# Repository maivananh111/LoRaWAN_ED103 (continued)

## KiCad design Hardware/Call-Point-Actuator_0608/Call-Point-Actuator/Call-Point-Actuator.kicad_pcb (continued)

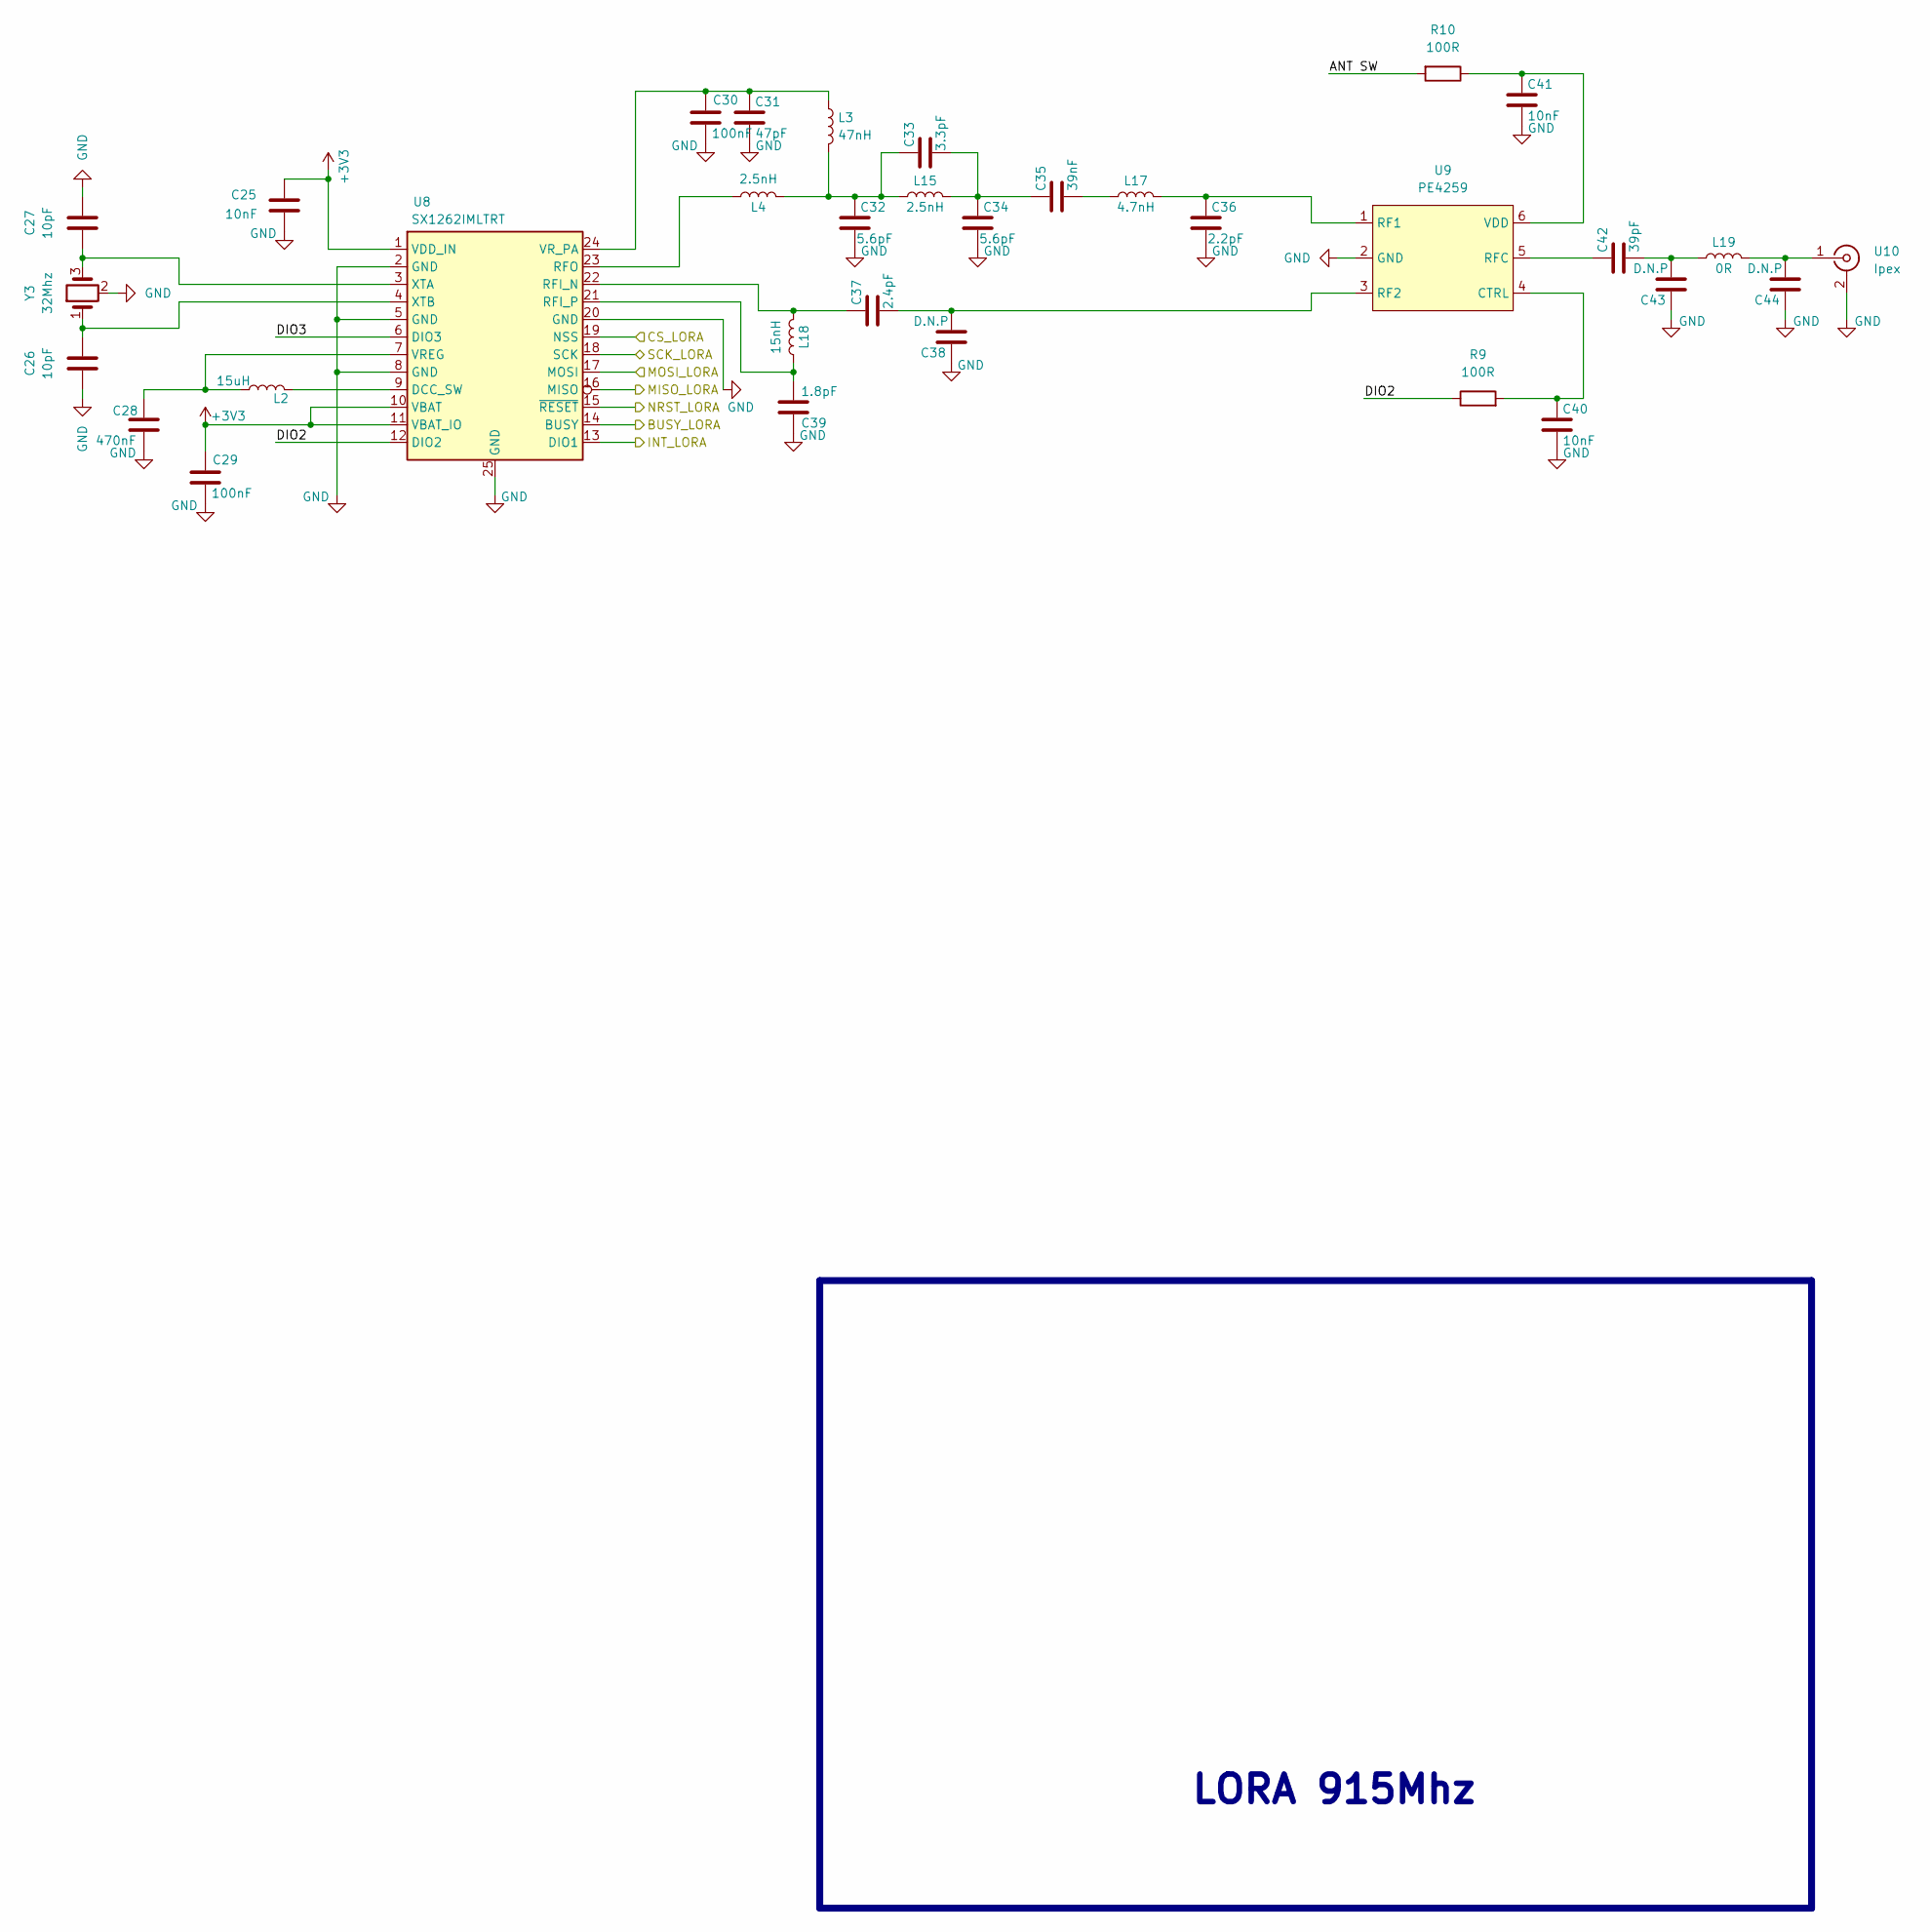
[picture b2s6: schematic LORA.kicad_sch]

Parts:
C25, C40, C41: 10nF; C_0603_1608Metric; JLC C43253
C26, C27: 10pF; C_0603_1608Metric; JLC C1634
C28: 470nF; C_0603_1608Metric; JLC C77572
C29, C30: 100nF; C_0603_1608Metric; JLC C14663
C31: 47pF; C_0603_1608Metric; JLC C105622
C32, C34: 5.6pF; C_0603_1608Metric; JLC C1674
C33: 3.3pF; C_0603_1608Metric; JLC C1660
C35: 39nF; C_0603_1608Metric; JLC C107091
C36: 2.2pF; C_0603_1608Metric; JLC C1651
C37: 2.4pF; C_0603_1608Metric; JLC C27741
C38, C43, C44: D.N.P; C_0603_1608Metric
C39: 1.8pF; C_0603_1608Metric; JLC C1640
C42: 39pF; C_0603_1608Metric; JLC C107049
L2: 15uH; L_0603; JLC C57838
L3: 47nH; L_0603; JLC C29683
L4, L15: 2.5nH; L_0603; JLC C370234
L17: 4.7nH; L_0603; JLC C1030
L18: 15nH; L_0603; JLC C23651
L19: 0R; L_0603; JLC C21189
R9, R10: 100R; L_0603_1608Metric; JLC C22775
U8: SX1262IMLTRT; QFN-24-1EP_4x4mm_P0.5mm_EP2.6x2.6mm
U9: PE4259; SOT-363_SC-70-6; JLC C470892
U10: Ipex; Conn_IPEX_ANT; JLC C496552
Y3: 32Mhz; Crystal_SMD_3225-4Pin_3.2x2.5mm; JLC C9009

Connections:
+3V3: C25.1, C29.1, U8.1 (VDD_IN), U8.10 (VBAT), U8.11 (VBAT_IO); also elsewhere on the board
/LORA/ANT SW: R10.2
/LORA/BUSY_LORA: U8.14 (BUSY); also elsewhere on the board
/LORA/CS_LORA: U8.19 (NSS); also elsewhere on the board
/LORA/DIO2: R9.1, U8.12 (DIO2)
/LORA/DIO3: U8.6 (DIO3)
/LORA/INT_LORA: U8.13 (DIO1); also elsewhere on the board
/LORA/MISO_LORA: U8.16 (MISO); also elsewhere on the board
/LORA/MOSI_LORA: U8.17 (MOSI); also elsewhere on the board
/LORA/NRST_LORA: U8.15 (~RESET); also elsewhere on the board
/LORA/SCK_LORA: U8.18 (SCK); also elsewhere on the board
GND: C25.2, C26.1, C27.2, C28.2, C29.2, C30.2, C31.2, C32.2, C34.2, C36.2, C38.1, C39.1, C40.2, C41.2, C43.1, C44.1, U8.2 (GND), U8.5 (GND), U8.8 (GND), U8.20 (GND), U8.25 (GND), U9.2 (GND), U10.2, U10.3, Y3.2, Y3.4; also elsewhere on the board
unnamed: C32.1, C33.1, L3.2, L4.2, L15.1
unnamed: C33.2, C34.1, C35.1, L15.2
unnamed: C35.2, L17.1
unnamed: C42.2, C43.2, L19.1
unnamed: C44.2, L19.2, U10.1
unnamed: L2.2, U8.9 (DCC_SW)
unnamed: C37.1, L18.2, U8.22 (RFI_N)
unnamed: C39.2, L18.1, U8.21 (RFI_P)
unnamed: L4.1, U8.23 (RFO)
unnamed: C28.1, L2.1, U8.7 (VREG)
unnamed: C30.1, C31.1, L3.1, U8.24 (VR_PA)
unnamed: C27.1, U8.3 (XTA), Y3.3
unnamed: C26.2, U8.4 (XTB), Y3.1
unnamed: C40.1, R9.2, U9.4 (CTRL)
unnamed: C36.1, L17.2, U9.1 (RF1)
unnamed: C37.2, C38.2, U9.3 (RF2)
unnamed: C42.1, U9.5 (RFC)
unnamed: C41.1, R10.1, U9.6 (VDD)

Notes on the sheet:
LORA 915Mhz

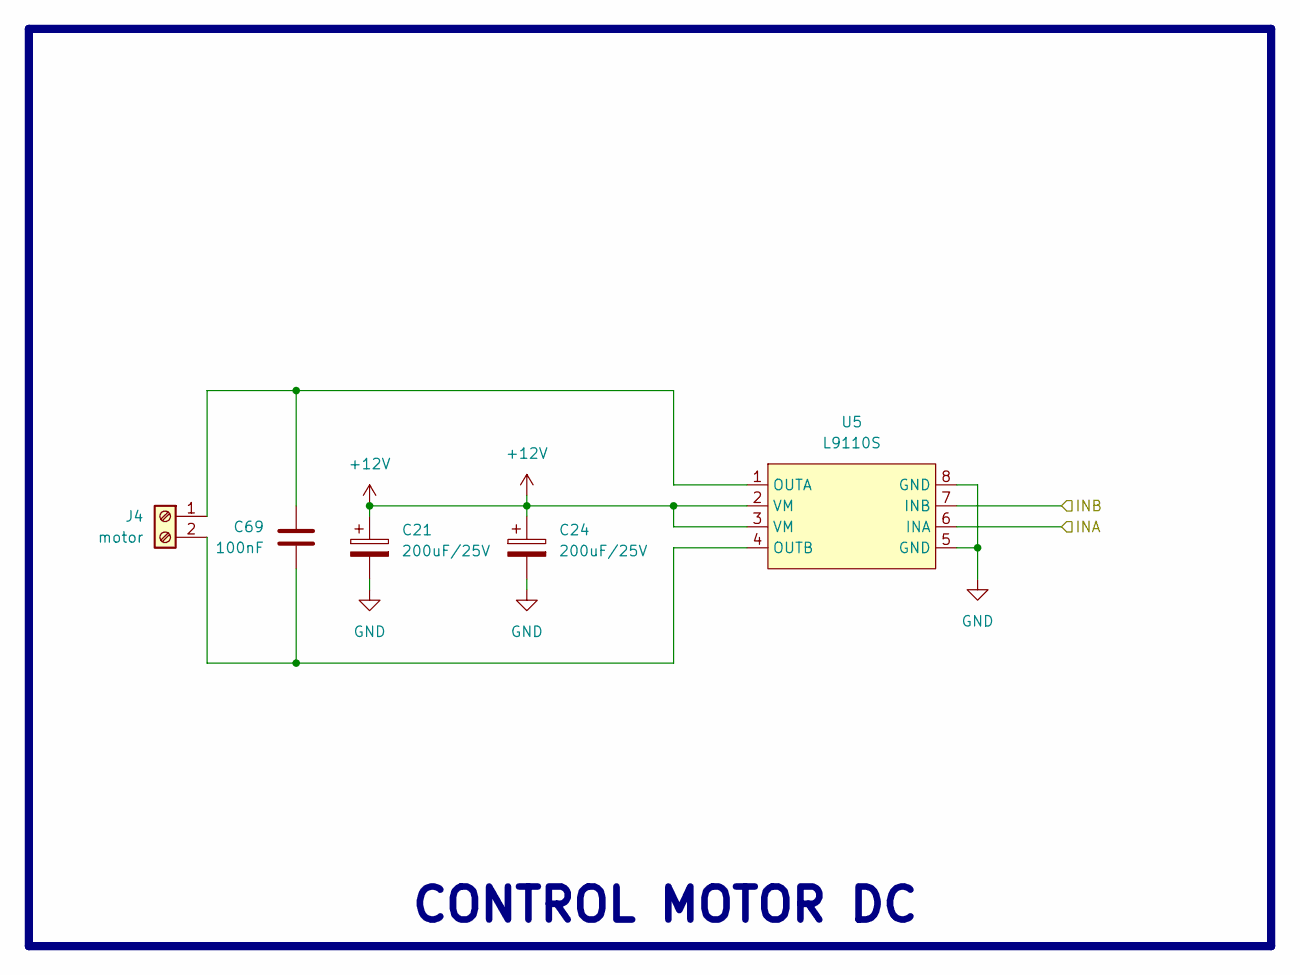
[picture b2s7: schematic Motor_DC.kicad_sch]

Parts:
C21, C24: 200uF/25V; C_TANTA_7343_CASE_E; JLC C132558
C69: 100nF; C_1206_3216Metric; JLC C525187
J4: motor; JST_PH_S2B-PH-SM4-TB_1x02-1MP_P2.00mm_Horizontal
U5: L9110S; SOP-8_3.9x4.9mm_P1.27mm; JLC C19272815

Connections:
+12V: C21.1, C24.1, U5.2 (VM), U5.3 (VM); also elsewhere on the board
/MCU/INA: U5.6 (INA); also elsewhere on the board
/MCU/INB: U5.7 (INB); also elsewhere on the board
GND: C21.2, C24.2, U5.5 (GND), U5.8 (GND); also elsewhere on the board
unnamed: C69.1, J4.1, U5.1 (OUTA)
unnamed: C69.2, J4.2, U5.4 (OUTB)

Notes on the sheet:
CONTROL MOTOR DC

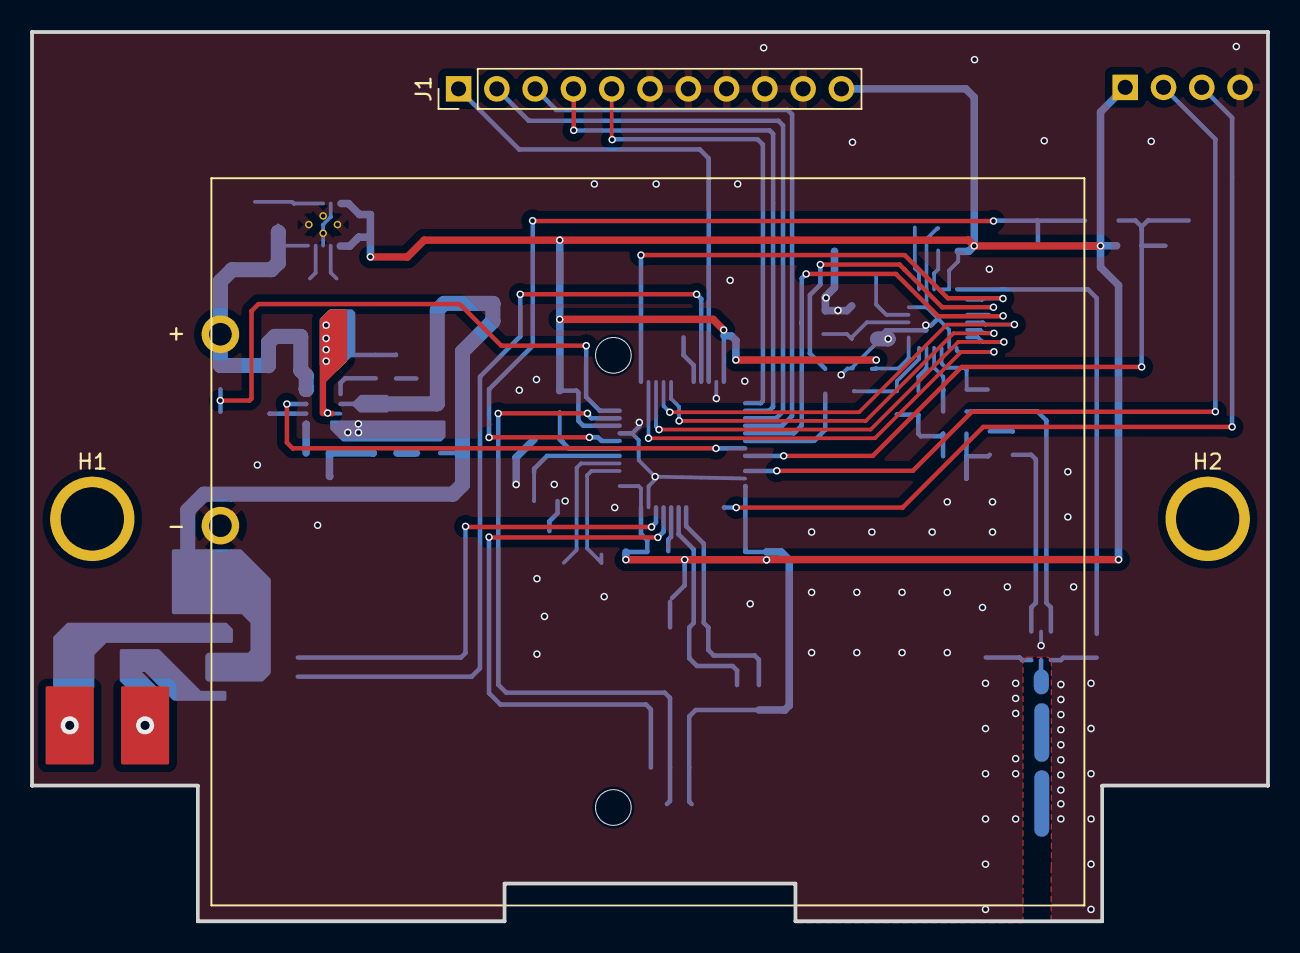
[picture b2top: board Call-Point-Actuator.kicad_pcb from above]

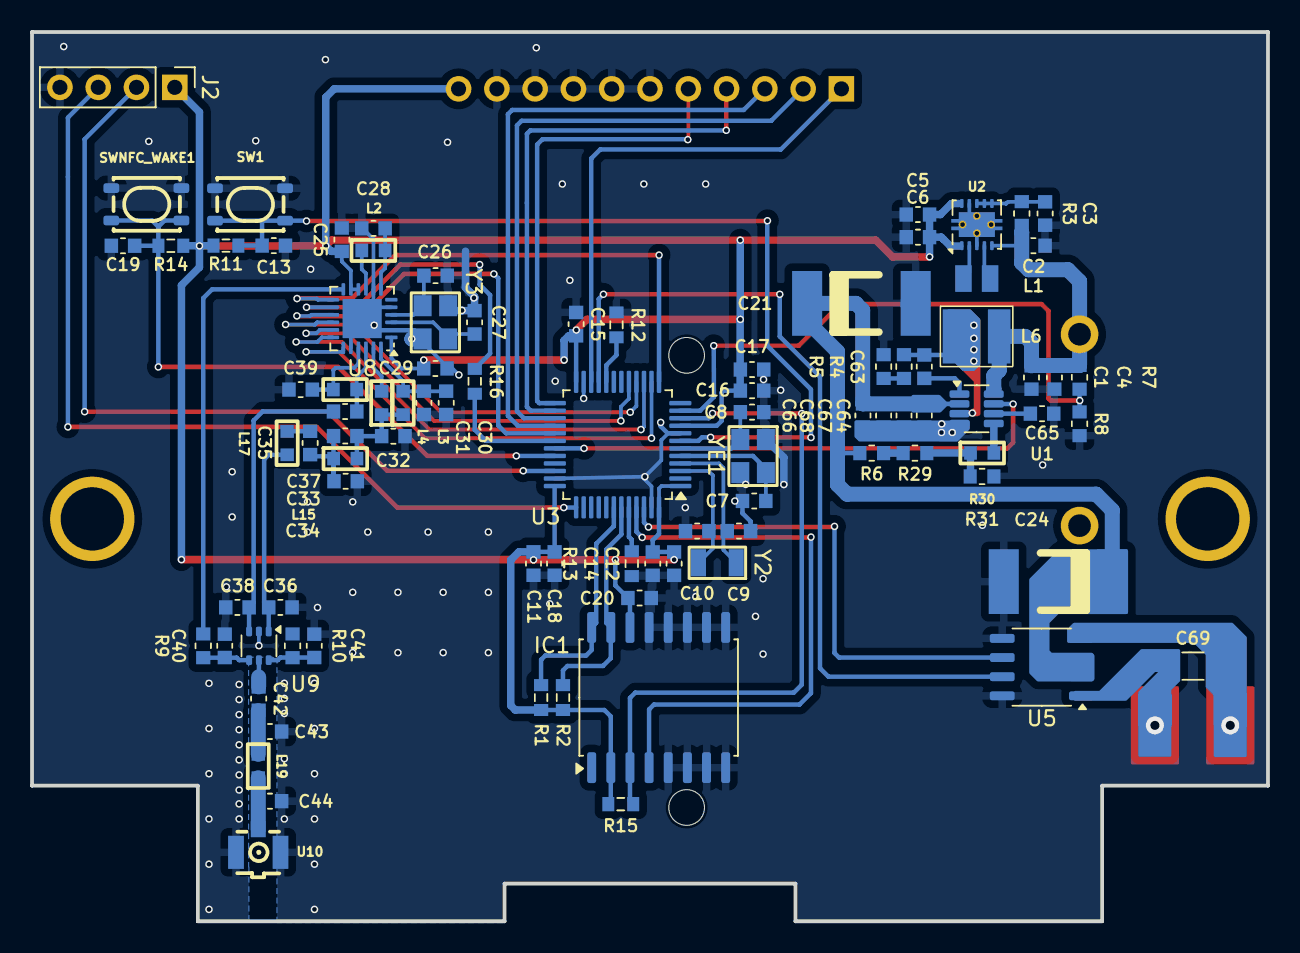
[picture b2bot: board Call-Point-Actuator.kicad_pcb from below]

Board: 2 copper layers, 82.0 x 59.0 mm, 95 parts (91 on the bottom side), 66 nets.

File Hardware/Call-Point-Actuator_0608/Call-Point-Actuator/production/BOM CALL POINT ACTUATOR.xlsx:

NAME | VALUE | FOOTPRINT | JLC | DigiKey Part Number
BT1 | Battery | DienLIB:BAT_BC3AAPC |  | BC3AAPC-ND
> C1, C4, C66-C68 | 22uF | C_0603_1608Metric | C84419
> C2, C5, C6 | 10uF | C_0603_1608Metric | C91150
> C3, C12-C16, C19, C20, C29, C30, C63, C64 | 100nF | C_0603_1608Metric | C116838
> C7, C8 | 12pF | C_0603_1608Metric | C1642
> C9, C10 | 9pF | C_0603_1608Metric | C513579
> C11, C65 | 4.7uF | C_0603_1608Metric | C76615
> C17, C25, C40, C41 | 10nF | C_0603_1608Metric | C43253
C18 | 1uF | C_0603_1608Metric | C126631
> C21, C24 | 200uF/25V | SANG_LIB_FP:C_TANTA_7343_CASE_E | C132558
> C26, C27 | 10pF | C_0603_1608Metric | C1634
C28 | 470nF | C_0603_1608Metric | C77572
C31 | 47pF | C_0603_1608Metric | C105622
> C32, C34 | 5.6pF | C_0603_1608Metric | C1674
C33 | 3.3pF | C_0603_1608Metric | C1660
C35 | 39nF | C_0603_1608Metric | C107091
C36 | 2.2pF | C_0603_1608Metric | C1651
C37 | 2.4pF | C_0603_1608Metric | C27741
C39 | 1.8pF | C_0603_1608Metric | C1640
C42 | 39pF | C_0603_1608Metric | C107049
C69 | 100nF | C_1206_3216Metric | C525187
IC1 | RTC_DS3231M | SOIC-16W_7.5x10.3mm_P1.27mm | NPN
J1 | Conn_01x11_Pin | PinHeader_1x11_P2.54mm_Vertical | C5116357
L1 | 2.2uH/1.5A | L_0806 | C439304
L2 | 15uH | L_0603 | C57838
L3 | 47nH | L_0603 | C29683
> L4, L15 | 2.5nH | L_0603 | C370234
L6 | 4.7uH | L_4040 | C167874
L17 | 4.7nH | L_0603 | C1030
L18 | 15nH | L_0603 | C23651
L19 | 0R | L_0603 | C21189
> R1, R2 | 4k7 | R_0603_1608Metric | C23162
> R3, R9, R10 | 100R | R_0603_1608Metric | C5123580
R6 | 680k | R_0603_1608Metric | C25822
R7 | 100k | R_0603_1608Metric | C667147
R8 | 200k | R_0603_1608Metric | C335089
> R11-R15 | 10k | R_0603_1608Metric | C25804
> R16, R30 | 0R | R_0603_1608Metric | C304185
R29 | 2k | R_0603_1608Metric | C72817
R31 | 62k | R_0603_1608Metric | C432812
> SW1, SWNFC_WAKE1 | SW_Tactile | SW_SPST_PTS810 | C221896
U1 | MP3437 | TSOT-23-8 |  | 1589-MP3437GJ-ZTR-ND - Tape & Reel (TR)
U2 | TPS63001 (fixed 3v3) | Package_SON:Texas_DRC0010J_ThermalVias | C28060
U3 | STM32U031C8T6 | Package_QFP:LQFP-48_7x7mm_P0.5mm |  | 497-STM32U031C8T6-ND
U5 | L9110S | Package_SO:SOP-8_3.9x4.9mm_P1.27mm | C19272815
U8 | SX1262IMLTRT | Package_DFN_QFN:QFN-24-1EP_4x4mm_P0.5mm_EP2.6x2.6mm |  | SX1262IMLTRTTR-ND - Tape & Reel (TR)
U9 | PE4259 | Package_TO_SOT_SMD:SOT-363_SC-70-6 | C470892
U10 | Ipex | DienLIB:Conn_IPEX_ANT | C496552
Y2 | 32.768kHz | Crystal_SMD_3215-2Pin_3.2x1.5mm | C620155
Y3 | 32Mhz | Crystal_SMD_3225-4Pin_3.2x2.5mm | C9009
Y1 | 8Mhz | Crystal_SMD_3225-4Pin_3.2x2.5mm | C400090

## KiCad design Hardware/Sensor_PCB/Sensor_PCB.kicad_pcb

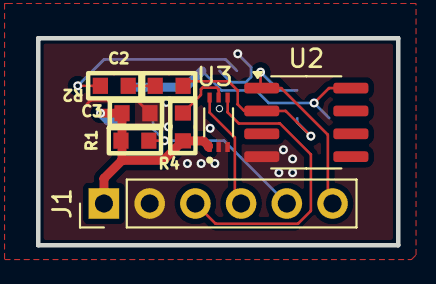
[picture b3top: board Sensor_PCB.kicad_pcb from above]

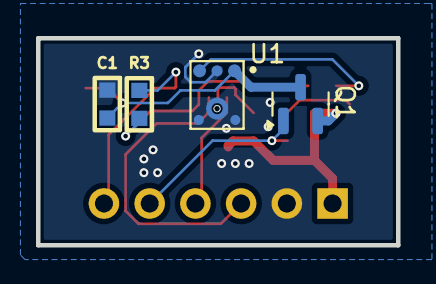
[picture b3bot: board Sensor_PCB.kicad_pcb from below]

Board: 2 copper layers, 20.0 x 11.5 mm, 12 parts (4 on the bottom side), 11 nets.

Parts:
C1, C2, C3: 100nF; C_0603
J1: 2.54; PinHeader_1x06_P2.54mm_Vertical
Q1: P_Mosfet; SOT-23
R1, R2, R3: 100k; R_0603
R4: 4k7; R_0603
U1: CMM-3729AB-38108-TR; MIC_CMM-3729AB-38108-TR
U2: LM358; SOIC-8_3.9x4.9mm_P1.27mm
U3: BH1750FVI-TR; XDCR_BH1750FVI-TR

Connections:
+3V3: C3.1, J1.1, Q1.2 (S), R1.1, R4.1, U3.1 (VCC)
/BH1750_SCL: J1.4, U3.6 (SCL)
/BH1750_SDA: J1.3, U3.4 (SDA)
/EN_Sound_sensor: J1.5, Q1.1 (G), R1.2
/Sound_sensor: J1.6, R3.2, U2.1
GND: C1.2, C3.2, J1.2, U1.2 (GND), U1.3 (GND), U1.5 (GND), U1.6 (GND), U2.4 (V-), U3.2 (ADDR), U3.3 (GND)
unnamed: C2.1, R2.1
unnamed: C1.1, Q1.3 (D), U1.1 (VDD), U2.8 (V+)
unnamed: C2.2, U1.4 (OUTPUT)
unnamed: R2.2, R3.1, U2.2 (-)
unnamed: R4.2, U3.5 (DVI)

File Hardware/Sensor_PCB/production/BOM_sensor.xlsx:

Designator | Footprint | Quantity | Value | LCSC Part # | Digikey
C1, C2, C3 | C_0603 | 3 | 100nF | C14663
J1 | PinHeader | 1 | 2.54 |  | A2-6PA-2.54DSA(81)-ND
Q1 | SOT-23 | 1 | P_Mosfet | C5261052
R1, R2, R3 | R_0603 | 3 | 100k | C14675
R4 | R_0603 | 1 | 4k7 | C23162
U1 | MIC_CMM-3729AB-38108-TR | 1 | CMM-3729AB-38108-TR |  | 102-5082-2-ND
U2 | SOIC-8_3.9x4.9mm_P1.27mm | 1 | LM358 | C9418
U3 | XDCR_BH1750FVI-TR | 1 | BH1750FVI-TR | C78960

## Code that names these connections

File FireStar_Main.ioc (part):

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Mcu.Name=STM32L451R(C-E)Tx
Mcu.Package=LQFP64
Mcu.UserName=STM32L451RETx
PA0.GPIOParameters=GPIO_Label
PA0.GPIO_Label=INT_RTC
PA0.Signal=GPIO_Input
PA1.GPIOParameters=GPIO_Label
PA1.GPIO_Label=Sound
PA1.Signal=ADCx_IN6
PA10.GPIOParameters=GPIO_Label
PA10.GPIO_Label=I2C_SDA
PA10.Mode=I2C
PA10.Signal=I2C1_SDA
PA13\ (JTMS/SWDIO).GPIOParameters=GPIO_Label
PA13\ (JTMS/SWDIO).GPIO_Label=SWDIO
PA13\ (JTMS/SWDIO).Mode=Serial_Wire
PA13\ (JTMS/SWDIO).Signal=SYS_JTMS-SWDIO
PA14\ (JTCK/SWCLK).Mode=Serial_Wire
PA14\ (JTCK/SWCLK).Signal=SYS_JTCK-SWCLK
PA15\ (JTDI).Signal=GPIO_Output
PA2.GPIOParameters=GPIO_Label
PA2.GPIO_Label=EN_Sound
PA2.Signal=GPIO_Output
PA3.GPIOParameters=PinState,GPIO_Label
PA3.GPIO_Label=LORA_RST
PA3.PinState=GPIO_PIN_SET
PA3.Signal=GPIO_Output
PA4.GPIOParameters=PinState,GPIO_Label
PA4.GPIO_Label=LORA_CS
PA4.PinState=GPIO_PIN_SET
PA4.Signal=GPIO_Output
PA5.GPIOParameters=GPIO_Label
PA5.GPIO_Label=SPI1_SCK
PA5.Mode=Full_Duplex_Master
PA5.Signal=SPI1_SCK
PA6.GPIOParameters=GPIO_Label
PA6.GPIO_Label=SPI1_MISO
PA6.Mode=Full_Duplex_Master
PA6.Signal=SPI1_MISO
PA7.GPIOParameters=GPIO_Label
PA7.GPIO_Label=SPI1_MOSI
PA7.Mode=Full_Duplex_Master
PA7.Signal=SPI1_MOSI
PA8.GPIOParameters=GPIO_Label
PA8.GPIO_Label=RST_RTC
PA8.Signal=GPIO_Output
PA9.GPIOParameters=GPIO_Label
PA9.GPIO_Label=I2C_SCL
PA9.Mode=I2C
PA9.Signal=I2C1_SCL
PB0.GPIOParameters=GPIO_Label
PB0.GPIO_Label=ADC_BAT
PB0.Signal=ADCx_IN15
PB1.GPIOParameters=GPIO_Label
PB1.GPIO_Label=MODE
PB1.Signal=GPIO_Output
PB10.GPIOParameters=GPIO_Label
PB10.GPIO_Label=INA
PB10.Signal=GPIO_Output
PB11.GPIOParameters=GPIO_Label
PB11.GPIO_Label=INB
PB11.Signal=GPIO_Output
PB12.GPIOParameters=GPIO_Label
PB12.GPIO_Label=CS_NFC
PB12.Signal=GPIO_Output
PB13.GPIOParameters=GPIO_Label
PB13.GPIO_Label=SPI2_SCK
PB13.Mode=Full_Duplex_Master
PB13.Signal=SPI2_SCK
PB14.GPIOParameters=GPIO_Label
PB14.GPIO_Label=SPI2_MISO
PB14.Mode=Full_Duplex_Master
PB14.Signal=SPI2_MISO
PB15.GPIOParameters=GPIO_Label
PB15.GPIO_Label=SPI2_MOSI
PB15.Mode=Full_Duplex_Master
PB15.Signal=SPI2_MOSI
PB6.Mode=Asynchronous
PB6.Signal=USART1_TX
PB7.Mode=Asynchronous
PB7.Signal=USART1_RX
PC0.GPIOParameters=GPIO_Label
PC0.GPIO_Label=HEATCOIL/ELEMENT
PC0.Signal=GPIO_Output
PC1.GPIOParameters=GPIO_Label
PC1.GPIO_Label=EN_HEAT
PC1.Signal=GPIO_Output
PC10.Mode=Full_Duplex_Master
PC10.Signal=SPI3_SCK
PC11.Mode=Full_Duplex_Master
PC11.Signal=SPI3_MISO
PC12.Mode=Full_Duplex_Master
PC12.Signal=SPI3_MOSI
PC14-OSC32_IN\ (PC14).GPIOParameters=GPIO_Label
PC14-OSC32_IN\ (PC14).GPIO_Label=PC14
PC14-OSC32_IN\ (PC14).Mode=LSE-External-Oscillator
PC14-OSC32_IN\ (PC14).Signal=RCC_OSC32_IN
PC15-OSC32_OUT\ (PC15).GPIOParameters=GPIO_Label
PC15-OSC32_OUT\ (PC15).GPIO_Label=PC15
PC15-OSC32_OUT\ (PC15).Mode=LSE-External-Oscillator
PC15-OSC32_OUT\ (PC15).Signal=RCC_OSC32_OUT
PC2.GPIOParameters=GPIO_Label
PC2.GPIO_Label=FAN
PC2.Signal=GPIO_Output
PC3.GPIOParameters=GPIO_Label
PC3.GPIO_Label=PUMP
PC3.Signal=GPIO_Output
PC4.GPIOParameters=GPIO_Label
PC4.GPIO_Label=LORA_INT
PC4.Signal=GPXTI4
PC5.GPIOParameters=GPIO_Label
PC5.GPIO_Label=LORA_BUSY
PC5.Signal=GPIO_Input
PC6.GPIOParameters=GPIO_Label
PC6.GPIO_Label=INT_NFC
PC6.Signal=GPIO_Input
PC7.GPIOParameters=GPIO_Label
PC7.GPIO_Label=EN_12V
PC7.Signal=GPIO_Output
PC8.GPIOParameters=GPIO_PuPd,GPIO_Label,GPIO_ModeDefaultEXTI
PC8.GPIO_Label=NFC_WAKE
PC8.GPIO_ModeDefaultEXTI=GPIO_MODE_IT_FALLING
PC8.GPIO_PuPd=GPIO_PULLUP
PC8.Signal=GPXTI8
RCC.HSE_VALUE=8000000
RCC.SYSCLKFreq_VALUE=48000000
board=custom

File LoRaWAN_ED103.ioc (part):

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Mcu.Name=STM32L431C(B-C)Tx
Mcu.Package=LQFP48
Mcu.UserName=STM32L431CCTx
PA1.GPIOParameters=GPIO_Label
PA1.GPIO_Label=ADC_BATT
PA1.Signal=ADCx_IN6
PA10.GPIOParameters=GPIO_Label
PA10.GPIO_Label=P12V_EN
PA10.Signal=GPIO_Output
PA11.GPIOParameters=GPIO_Label,GPIO_ModeDefaultEXTI
PA11.GPIO_Label=BTN_WAKE
PA11.GPIO_ModeDefaultEXTI=GPIO_MODE_IT_FALLING
PA11.Signal=GPXTI11
PA13\ (JTMS-SWDIO).Mode=Serial_Wire
PA13\ (JTMS-SWDIO).Signal=SYS_JTMS-SWDIO
PA14\ (JTCK-SWCLK).Mode=Serial_Wire
PA14\ (JTCK-SWCLK).Signal=SYS_JTCK-SWCLK
PA3.GPIOParameters=GPIO_Label
PA3.GPIO_Label=LORA_INT
PA3.Signal=GPXTI3
PA4.GPIOParameters=PinState,GPIO_Label
PA4.GPIO_Label=LORA_CS
PA4.PinState=GPIO_PIN_SET
PA4.Signal=GPIO_Output
PA5.Mode=Full_Duplex_Master
PA5.Signal=SPI1_SCK
PA6.Mode=Full_Duplex_Master
PA6.Signal=SPI1_MISO
PA7.Mode=Full_Duplex_Master
PA7.Signal=SPI1_MOSI
PA8.GPIOParameters=PinState,GPIO_Label
PA8.GPIO_Label=LORA_RST
PA8.PinState=GPIO_PIN_SET
PA8.Signal=GPIO_Output
PA9.GPIOParameters=GPIO_Label
PA9.GPIO_Label=LORA_BUSY
PA9.Signal=GPIO_Input
PB10.GPIOParameters=GPIO_Label
PB10.GPIO_Label=INB
PB10.Signal=GPIO_Output
PB6.Mode=Asynchronous
PB6.Signal=USART1_TX
PB7.Mode=Asynchronous
PB7.Signal=USART1_RX
PB9.GPIOParameters=GPIO_Label
PB9.GPIO_Label=INA
PB9.Signal=GPIO_Output
PC14-OSC32_IN\ (PC14).Mode=LSE-External-Oscillator
PC14-OSC32_IN\ (PC14).Signal=RCC_OSC32_IN
PC15-OSC32_OUT\ (PC15).Mode=LSE-External-Oscillator
PC15-OSC32_OUT\ (PC15).Signal=RCC_OSC32_OUT
RCC.HSE_VALUE=8000000
RCC.SYSCLKFreq_VALUE=48000000
board=custom

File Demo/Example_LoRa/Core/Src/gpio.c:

/* USER CODE BEGIN Header */
/**
  ******************************************************************************
  * @file    gpio.c
  * @brief   This file provides code for the configuration
  *          of all used GPIO pins.
  ******************************************************************************
  * @attention
  *
  * Copyright (c) 2024 STMicroelectronics.
  * All rights reserved.
  *
  * This software is licensed under terms that can be found in the LICENSE file
  * in the root directory of this software component.
  * If no LICENSE file comes with this software, it is provided AS-IS.
  *
  ******************************************************************************
  */
/* USER CODE END Header */

/* Includes ------------------------------------------------------------------*/
#include "gpio.h"

/* USER CODE BEGIN 0 */

/* USER CODE END 0 */

/*----------------------------------------------------------------------------*/
/* Configure GPIO                                                             */
/*----------------------------------------------------------------------------*/
/* USER CODE BEGIN 1 */

/* USER CODE END 1 */

/** Configure pins
     PA13 (SWDIO)   ------> DEBUG_JTMS-SWDIO
     PA14 (SWCLK)   ------> DEBUG_JTCK-SWCLK
*/
void MX_GPIO_Init(void)
{

  GPIO_InitTypeDef GPIO_InitStruct = {0};

  /* GPIO Ports Clock Enable */
  __HAL_RCC_GPIOC_CLK_ENABLE();
  __HAL_RCC_GPIOF_CLK_ENABLE();
  __HAL_RCC_GPIOA_CLK_ENABLE();
  __HAL_RCC_GPIOB_CLK_ENABLE();

  /*Configure GPIO pin Output Level */
  HAL_GPIO_WritePin(GPIOA, LORA_CS_Pin|LORA_RST_Pin, GPIO_PIN_SET);

  /*Configure GPIO pins : PC13 PC14 PC15 */
  GPIO_InitStruct.Pin = GPIO_PIN_13|GPIO_PIN_14|GPIO_PIN_15;
  GPIO_InitStruct.Mode = GPIO_MODE_ANALOG;
  GPIO_InitStruct.Pull = GPIO_NOPULL;
  HAL_GPIO_Init(GPIOC, &GPIO_InitStruct);

  /*Configure GPIO pins : PF0 PF1 PF2 PF3 */
  GPIO_InitStruct.Pin = GPIO_PIN_0|GPIO_PIN_1|GPIO_PIN_2|GPIO_PIN_3;
  GPIO_InitStruct.Mode = GPIO_MODE_ANALOG;
  GPIO_InitStruct.Pull = GPIO_NOPULL;
  HAL_GPIO_Init(GPIOF, &GPIO_InitStruct);

  /*Configure GPIO pins : PA0 PA1 PA2 PA10
                           PA12 PA15 */
  GPIO_InitStruct.Pin = GPIO_PIN_0|GPIO_PIN_1|GPIO_PIN_2|GPIO_PIN_10
                          |GPIO_PIN_12|GPIO_PIN_15;
  GPIO_InitStruct.Mode = GPIO_MODE_ANALOG;
  GPIO_InitStruct.Pull = GPIO_NOPULL;
  HAL_GPIO_Init(GPIOA, &GPIO_InitStruct);

  /*Configure GPIO pin : PtPin */
  GPIO_InitStruct.Pin = LORA_INT_Pin;
  GPIO_InitStruct.Mode = GPIO_MODE_IT_RISING;
  GPIO_InitStruct.Pull = GPIO_NOPULL;
  HAL_GPIO_Init(LORA_INT_GPIO_Port, &GPIO_InitStruct);

  /*Configure GPIO pins : PAPin PAPin */
  GPIO_InitStruct.Pin = LORA_CS_Pin|LORA_RST_Pin;
  GPIO_InitStruct.Mode = GPIO_MODE_OUTPUT_PP;
  GPIO_InitStruct.Pull = GPIO_NOPULL;
  GPIO_InitStruct.Speed = GPIO_SPEED_FREQ_LOW;
  HAL_GPIO_Init(GPIOA, &GPIO_InitStruct);

  /*Configure GPIO pins : PB0 PB1 PB2 PB10
                           PB11 PB12 PB13 PB14
                           PB15 PB3 PB4 PB5
                           PB6 PB7 PB8 PB9 */
  GPIO_InitStruct.Pin = GPIO_PIN_0|GPIO_PIN_1|GPIO_PIN_2|GPIO_PIN_10
                          |GPIO_PIN_11|GPIO_PIN_12|GPIO_PIN_13|GPIO_PIN_14
                          |GPIO_PIN_15|GPIO_PIN_3|GPIO_PIN_4|GPIO_PIN_5
                          |GPIO_PIN_6|GPIO_PIN_7|GPIO_PIN_8|GPIO_PIN_9;
  GPIO_InitStruct.Mode = GPIO_MODE_ANALOG;
  GPIO_InitStruct.Pull = GPIO_NOPULL;
  HAL_GPIO_Init(GPIOB, &GPIO_InitStruct);

  /*Configure GPIO pin : PtPin */
  GPIO_InitStruct.Pin = LORA_BUSY_Pin;
  GPIO_InitStruct.Mode = GPIO_MODE_INPUT;
  GPIO_InitStruct.Pull = GPIO_NOPULL;
  HAL_GPIO_Init(LORA_BUSY_GPIO_Port, &GPIO_InitStruct);

  /*Configure GPIO pin : PtPin */
  GPIO_InitStruct.Pin = BTN_WAKE_Pin;
  GPIO_InitStruct.Mode = GPIO_MODE_IT_FALLING;
  GPIO_InitStruct.Pull = GPIO_NOPULL;
  HAL_GPIO_Init(BTN_WAKE_GPIO_Port, &GPIO_InitStruct);

  /* EXTI interrupt init*/
  HAL_NVIC_SetPriority(EXTI2_3_IRQn, 0, 0);
  HAL_NVIC_EnableIRQ(EXTI2_3_IRQn);

  HAL_NVIC_SetPriority(EXTI4_15_IRQn, 0, 0);
  HAL_NVIC_EnableIRQ(EXTI4_15_IRQn);

}

/* USER CODE BEGIN 2 */

/* USER CODE END 2 */

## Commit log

2024-10-16 nay 16/10 con bug
2024-10-20 Features += (Join exponential backoff + Device request time MAC);
2024-10-20 Features += (bootup + regular_checks)
2024-10-20 Features += (preactivation + activation), not tested
2024-10-30 No commit.
2024-11-03 Fixed: Retry delay, device time request, rejoin
2024-11-04 ADR on
2024-11-21 The problem is in the FQ value.
2024-11-22 Remove some unused log.
2024-11-22 Changed application name macro.
2024-11-22 Add button start activation feature.
2024-11-22 fix error button doesn't work when it is not connected.
2025-01-06 Change log timestamp.
